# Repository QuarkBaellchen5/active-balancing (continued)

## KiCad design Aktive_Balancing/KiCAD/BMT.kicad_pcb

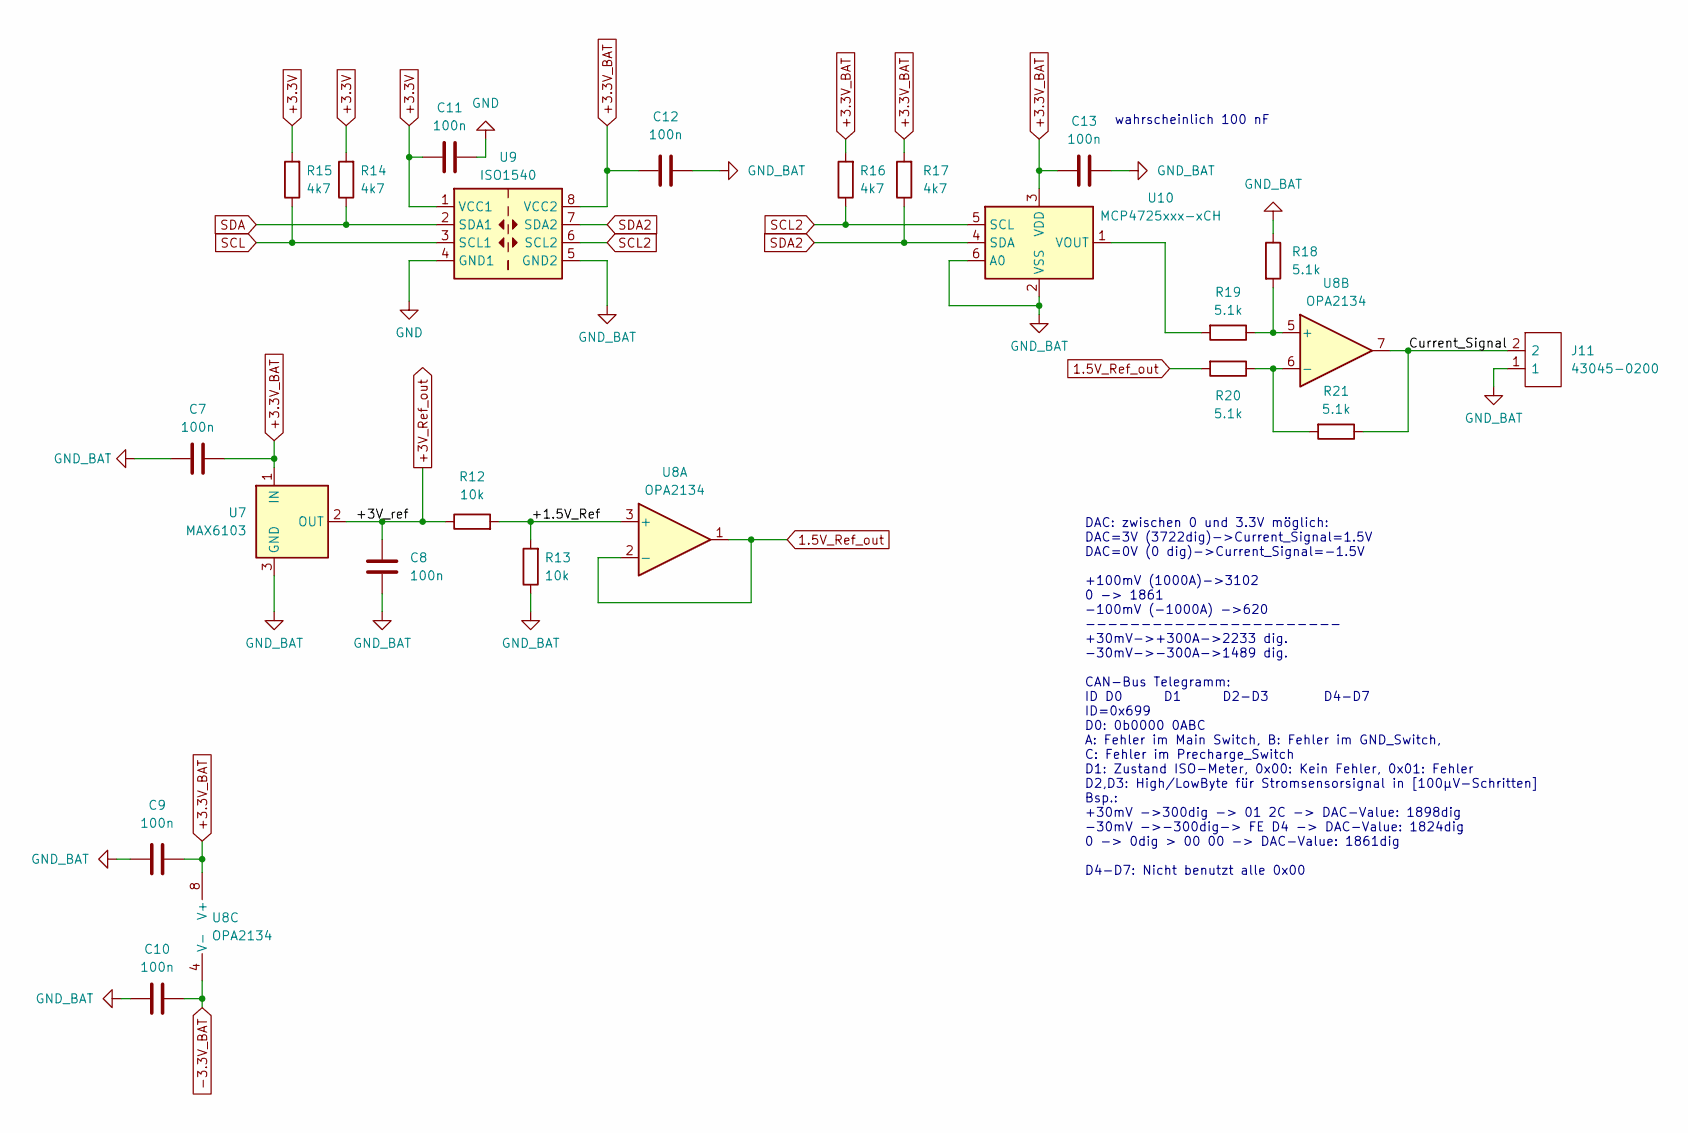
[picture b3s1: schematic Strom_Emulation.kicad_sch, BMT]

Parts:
C7, C8, C9, C10, C11, C12, C13: 100n; C_0603_1608Metric_Pad1.08x0.95mm_HandSolder
J11: 43045-0200; Manufacturer_Part_Number 43045-0200
R12, R13: 10k; R_0603_1608Metric
R14, R15, R16, R17: 4k7; R_0603_1608Metric
R18, R19, R20, R21: 5.1k; R_0603_1608Metric
U7: MAX6103; SOT-23
U8: OPA2134; SO-8_3.9x4.9mm_P1.27mm
U9: ISO1540; SOIC-8_3.9x4.9mm_P1.27mm; Mouser Part No 595-ISO1540DR
U10: MCP4725xxx-xCH; SOT-23-6; Mouser Part No 579-MCP4725A0TECH

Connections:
1.5V_Ref_out: R20.2, U8.1, U8.2 (-)
+3.3V: C11.1, R14.2, R15.2, U9.1 (VCC1); also elsewhere on the board
+3.3V_BAT: C7.2, C9.2, C12.1, C13.1, R16.2, R17.2, U7.1 (IN), U8.8 (V+), U9.8 (VCC2), U10.3 (VDD); also elsewhere on the board
+3V_Ref_out: C8.2, R12.1, U7.2 (OUT)
-3.3V_BAT: C10.2, U8.4 (V-); also elsewhere on the board
/Strom_Emulation/+1.5V_Ref: R12.2, R13.2, U8.3 (+)
/Strom_Emulation/Current_Signal: J11.2, R21.1, U8.7
GND: C11.2, U9.4 (GND1); also elsewhere on the board
GND_BAT: C7.1, C8.1, C9.1, C10.1, C12.2, C13.2, J11.1, R13.1, R18.1, U7.3 (GND), U9.5 (GND2), U10.2 (VSS), U10.6 (A0); also elsewhere on the board
unnamed: R18.2, R19.1, U8.5 (+)
unnamed: R20.1, R21.2, U8.6 (-)
unnamed: R19.2, U10.1 (VOUT)
SCL: R15.1, U9.3 (SCL1); also elsewhere on the board
SCL2: R16.1, U9.6 (SCL2), U10.5 (SCL)
SDA: R14.1, U9.2 (SDA1); also elsewhere on the board
SDA2: R17.1, U9.7 (SDA2), U10.4 (SDA)

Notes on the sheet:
wahrscheinlich 100 nF
DAC: zwischen 0 und 3.3V möglich: DAC=3V (3722dig)->Current_Signal=1.5V DAC=0V (0 dig)->Current_Signal=-1.5V +100mV (1000A)->3102 0 -> 1861 -100mV (-1000A) ->620 ----------------------- +30mV->+300A->2233 dig. -30mV->-300A->1489 dig. CAN-Bus Telegramm: ID D0 D1 D2-D3 D4-D7 ID=0x699 D0: 0b0000 0ABC 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

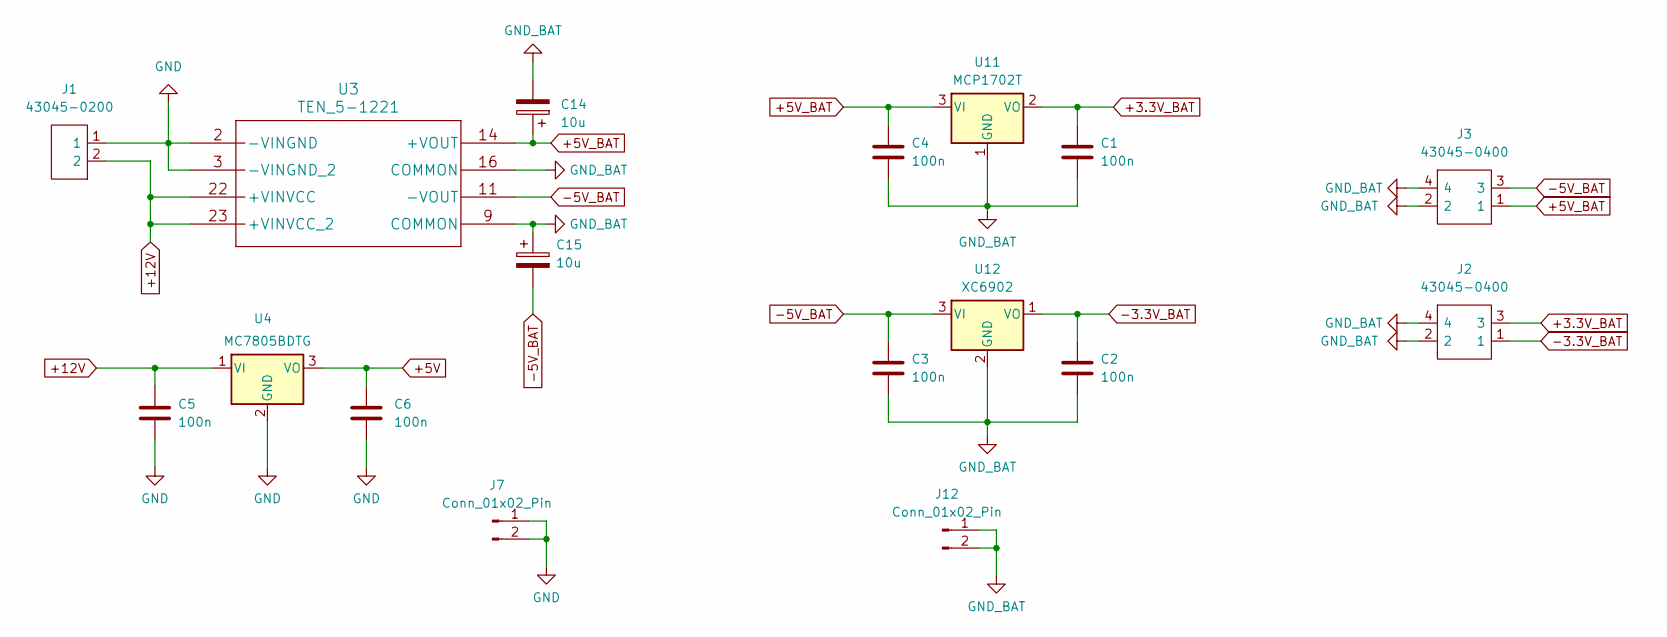
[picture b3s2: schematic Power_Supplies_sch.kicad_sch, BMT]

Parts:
C1, C2, C3, C4, C5, C6: 100n; C_0603_1608Metric_Pad1.08x0.95mm_HandSolder
C14, C15: 10u; CP_Elec_6.3x3.9
J1: 43045-0200; Manufacturer_Part_Number 43045-0200
J2, J3: 43045-0400; Manufacturer_Part_Number 43045-0400
J7, J12: Conn_01x02_Pin; PinHeader_1x02_P2.54mm_Vertical
U3: TEN_5-1221; TEN5_TRP
U4: MC7805BDTG; TO-252-3_TabPin4; Mouser Part No 863-MC7805CDTG
U11: MCP1702T; SOT-23; MANUFACTURER_PART_NUMBER MCP1702T-3302E/CB
U12: XC6902; SOT-23; MANUFACTURER_PART_NUMBER XC6902N331MR-G

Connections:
+3.3V_BAT: C1.1, J2.3, U11.2 (VO); also elsewhere on the board
+5V: C6.1, U4.3 (VO); also elsewhere on the board
+5V_BAT: C4.1, C14.1, J3.1, U3.14 (+VOUT), U11.3 (VI)
+12V: C5.1, J1.2, U3.22 (+VINVCC), U3.23 (+VINVCC_2), U4.1 (VI); also elsewhere on the board
-3.3V_BAT: C2.1, J2.1, U12.1 (VO); also elsewhere on the board
-5V_BAT: C3.1, C15.2, J3.3, U3.11 (-VOUT), U12.3 (VI)
GND: C5.2, C6.2, J1.1, J7.1, J7.2, U3.2 (-VINGND), U3.3 (-VINGND_2), U4.2 (GND); also elsewhere on the board
GND_BAT: C1.2, C2.2, C3.2, C4.2, C14.2, C15.1, J2.2, J2.4, J3.2, J3.4, J12.1, J12.2, U3.9 (COMMON), U3.16 (COMMON), U11.1 (GND), U12.2 (GND); also elsewhere on the board

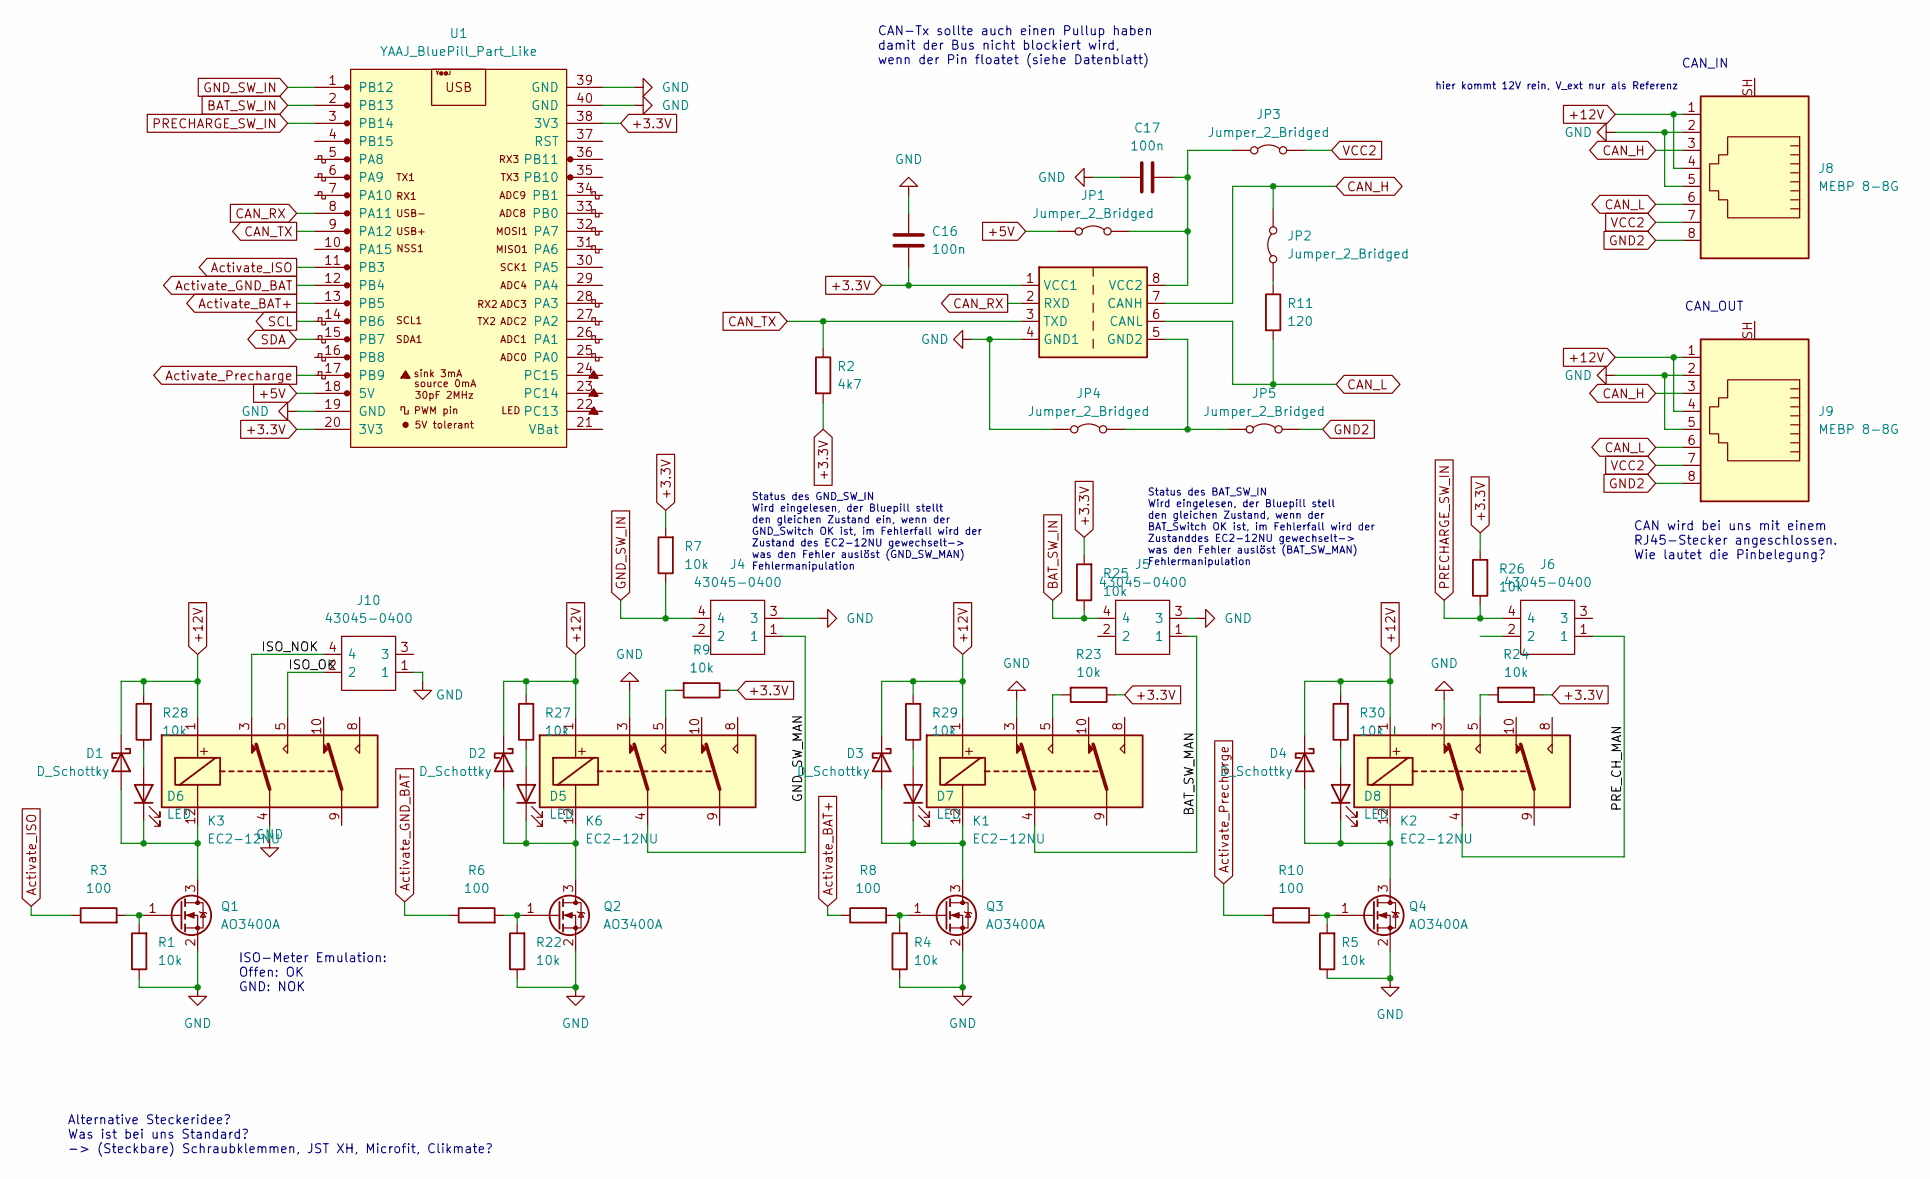
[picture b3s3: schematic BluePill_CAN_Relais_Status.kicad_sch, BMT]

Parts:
C16, C17: 100n; C_0603_1608Metric_Pad1.08x0.95mm_HandSolder
D1, D2, D3, D4: D_Schottky; D_SOD-323_HandSoldering; MANUFACTURER_PART_NUMBER 1N5819WS; LCSC Part Number C191023
D5, D6, D7, D8: LED; LED_0603_1608Metric_Pad1.05x0.95mm_HandSolder
J4, J5, J6, J10: 43045-0400; Manufacturer_Part_Number 43045-0400
J8, J9: MEBP 8-8G
JP1, JP2, JP3, JP4, JP5: Jumper_2_Bridged; PinHeader_1x02_P2.54mm_Vertical
K1, K2, K3, K6: EC2-12NU; Relay_DPDT_Kemet_EC2
Q1, Q2, Q3, Q4: AO3400A; SOT-23
R1, R4, R5, R7, R9, R22, R23, R24, R25, R26, R27, R28, R29, R30: 10k; R_0603_1608Metric
R2: 4k7; R_0603_1608Metric
R3, R6, R8, R10: 100; R_0603_1608Metric
R11: 120; R_0603_1608Metric
U1: YAAJ_BluePill_Part_Like; YAAJ_BluePill_1
U2: ISO1050DUB; SOP-8_6.62x9.15mm_P2.54mm

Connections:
+3.3V: C16.2, R2.2, R7.2, R9.1, R23.1, R24.1, R25.2, R26.2, U1.20 (3V3), U1.38 (3V3), U2.1 (VCC1); also elsewhere on the board
+5V: JP1.1 (A), U1.18 (5V); also elsewhere on the board
+12V: D1.1 (K), D2.1 (K), D3.1 (K), D4.1 (K), J8.1, J8.4, J9.1, J9.4, K1.1, K2.1, K3.1, K6.1, R27.2, R28.2, R29.2, R30.2; also elsewhere on the board
/BluePill_CAN_Relais_Status/BAT_SW_MAN: J5.1, K1.4
/BluePill_CAN_Relais_Status/GND_SW_MAN: J4.1, K6.4
/BluePill_CAN_Relais_Status/ISO_NOK: J10.4, K3.3
/BluePill_CAN_Relais_Status/ISO_OK: J10.2, K3.5
/BluePill_CAN_Relais_Status/PRE_CH_MAN: J6.1, K2.4
Activate_BAT+: R8.1, U1.13 (PB5)
Activate_GND_BAT: R6.1, U1.12 (PB4)
Activate_ISO: R3.1, U1.11 (PB3)
Activate_Precharge: R10.1, U1.17 (PB9)
BAT_SW_IN: J5.4, R25.1, U1.2 (PB13)
CAN_H: J8.3, J9.3, JP2.2 (B), U2.7 (CANH)
CAN_L: J8.6, J9.6, R11.2, U2.6 (CANL)
CAN_RX: U1.8 (PA11), U2.2 (RXD)
CAN_TX: R2.1, U1.9 (PA12), U2.3 (TXD)
GND: C16.1, C17.1, J4.3, J5.3, J8.2, J8.5, J9.2, J9.5, J10.1, JP4.1 (A), K1.3, K2.3, K3.4, K6.3, Q1.2 (S), Q2.2 (S), Q3.2 (S), Q4.2 (S), R1.1, R4.1, R5.1, R22.1, U1.19 (GND), U1.39 (GND), U1.40 (GND), U2.4 (GND1); also elsewhere on the board
GND2: J8.8, J9.8, JP5.2 (B)
GND_SW_IN: J4.4, R7.1, U1.1 (PB12)
unnamed: D1.2 (A), D6.1 (K), K3.12, Q1.3 (D)
unnamed: D2.2 (A), D5.1 (K), K6.12, Q2.3 (D)
unnamed: D3.2 (A), D7.1 (K), K1.12, Q3.3 (D)
unnamed: D4.2 (A), D8.1 (K), K2.12, Q4.3 (D)
unnamed: D5.2 (A), R27.1
unnamed: D6.2 (A), R28.1
unnamed: D7.2 (A), R29.1
unnamed: D8.2 (A), R30.1
unnamed: C17.2, JP1.2 (B), JP3.1 (A), U2.8 (VCC2)
unnamed: JP2.1 (A), R11.1
unnamed: JP4.2 (B), JP5.1 (A), U2.5 (GND2)
unnamed: K1.5, R23.2
unnamed: K2.5, R24.2
unnamed: K6.5, R9.2
unnamed: Q1.1 (G), R1.2, R3.2
unnamed: Q2.1 (G), R6.2, R22.2
unnamed: Q3.1 (G), R4.2, R8.2
unnamed: Q4.1 (G), R5.2, R10.2
PRECHARGE_SW_IN: J6.4, R26.1, U1.3 (PB14)
SCL: U1.14 (PB6); also elsewhere on the board
SDA: U1.15 (PB7); also elsewhere on the board
VCC2: J8.7, J9.7, JP3.2 (B)

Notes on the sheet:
Status des GND_SW_IN Wird eingelesen, der Bluepill stellt den gleichen Zustand ein, wenn der GND_Switch OK ist, im Fehlerfall wird der Zustand des EC2-12NU gewechselt-> was den Fehler auslöst (GND_SW_MAN) Fehlermanipulation
ISO-Meter Emulation: Offen: OK GND: NOK
CAN-Tx sollte auch einen Pullup haben damit der Bus nicht blockiert wird, wenn der Pin floatet (siehe Datenblatt)
Alternative Steckeridee? Was ist bei uns Standard? -> (Steckbare) Schraubklemmen, JST XH, Microfit, Clikmate?
CAN_OUT
CAN wird bei uns mit einem RJ45-Stecker angeschlossen. Wie lautet die Pinbelegung?
Status des BAT_SW_IN Wird eingelesen, der Bluepill stell den gleichen Zustand, wenn der BAT_Switch OK ist, im Fehlerfall wird der Zustanddes EC2-12NU gewechselt-> was den Fehler auslöst (BAT_SW_MAN) Fehlermanipulation
hier kommt 12V rein, V_ext nur als Referenz
CAN_IN

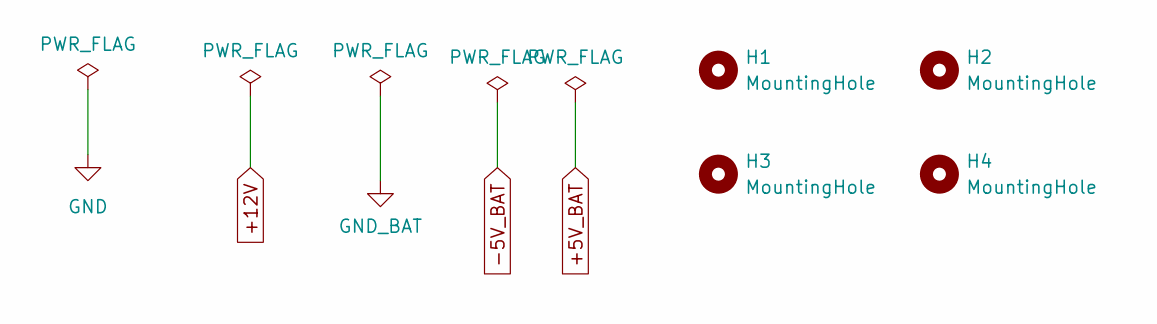
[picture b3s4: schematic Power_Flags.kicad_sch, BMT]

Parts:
H1, H2, H3, H4: MountingHole; MountingHole_3.2mm_M3_DIN965_Pad

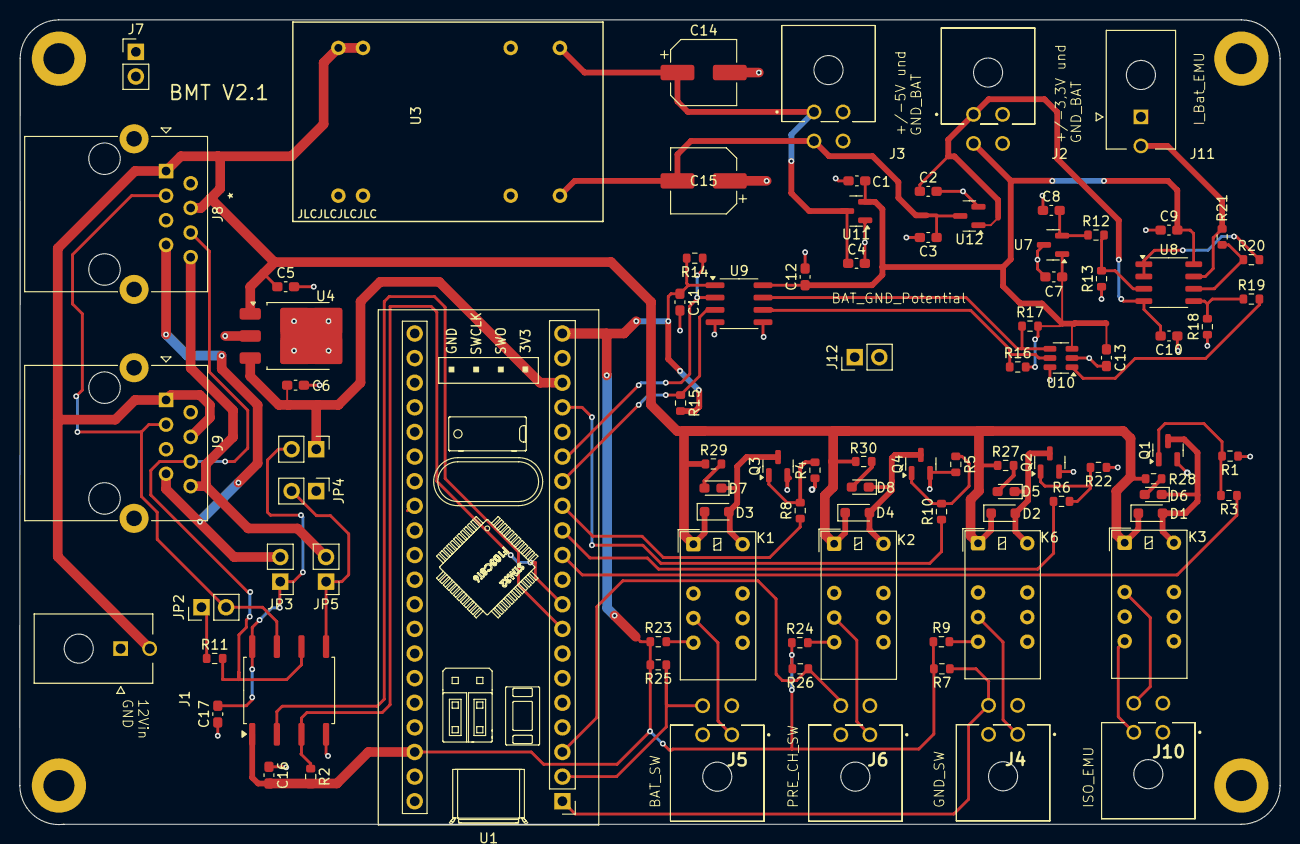
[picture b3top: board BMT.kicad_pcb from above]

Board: 2 copper layers, 130.0 x 83.0 mm, 94 parts (0 on the bottom side), 56 nets.

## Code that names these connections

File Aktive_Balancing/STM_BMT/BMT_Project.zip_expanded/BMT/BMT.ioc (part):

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Mcu.Name=STM32F103C(8-B)Tx
Mcu.Package=LQFP48
Mcu.UserName=STM32F103C8Tx
PA11.GPIOParameters=GPIO_PuPd
PA11.GPIO_PuPd=GPIO_PULLUP
PA11.Mode=CAN_Activate
PA11.Signal=CAN_RX
PA12.GPIOParameters=GPIO_Speed
PA12.GPIO_Speed=GPIO_SPEED_FREQ_HIGH
PA12.Mode=CAN_Activate
PA12.Signal=CAN_TX
PA13.Mode=Serial_Wire
PA13.Signal=SYS_JTMS-SWDIO
PA14.Mode=Serial_Wire
PA14.Signal=SYS_JTCK-SWCLK
PB12.GPIOParameters=GPIO_Label
PB12.GPIO_Label=GND_SW_IN
PB12.Signal=GPIO_Input
PB13.GPIOParameters=GPIO_Label
PB13.GPIO_Label=BAT_SW_in
PB13.Signal=GPIO_Input
PB14.GPIOParameters=GPIO_Label
PB14.GPIO_Label=PreCh_SW_in
PB14.Signal=GPIO_Input
PB3.GPIOParameters=GPIO_Label
PB3.GPIO_Label=Activate_ISO
PB3.Signal=GPIO_Output
PB4.GPIOParameters=GPIO_Label
PB4.GPIO_Label=Activate_GND_BAT
PB4.Signal=GPIO_Output
PB5.GPIOParameters=GPIO_Label
PB5.GPIO_Label=Avtivate_Bat_Plus
PB5.Signal=GPIO_Output
PB6.GPIOParameters=GPIO_Speed
PB6.GPIO_Speed=GPIO_SPEED_FREQ_HIGH
PB6.Mode=I2C
PB6.Signal=I2C1_SCL
PB7.GPIOParameters=GPIO_Speed
PB7.GPIO_Speed=GPIO_SPEED_FREQ_HIGH
PB7.Mode=I2C
PB7.Signal=I2C1_SDA
PB9.GPIOParameters=GPIO_Label
PB9.GPIO_Label=Acivate_Precharche
PB9.Signal=GPIO_Output
PD0-OSC_IN.Mode=HSE-External-Oscillator
PD0-OSC_IN.Signal=RCC_OSC_IN
PD1-OSC_OUT.Mode=HSE-External-Oscillator
PD1-OSC_OUT.Signal=RCC_OSC_OUT
RCC.SYSCLKFreq_VALUE=72000000
RCC.SYSCLKSource=RCC_SYSCLKSOURCE_PLLCLK
board=custom

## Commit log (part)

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2026-04-02 add gittignore for LTSpice
2026-04-06 Eingerichtet
2026-04-06 temp save
2026-04-06 OPamp ersetzt durch realen OP
    Der Opamp2 hab ich jetzt ersetzt gegen einen realen OP den LT1007
2026-04-06 Schalter gegen Mosfet
    versucht den schalter zu tauschen aber der strom wird dann nicht mehr geregelt
2026-04-06 schalter getauscht
2026-04-07 added models for LT
    Dateien hinzugefügt
    für Infineon Fets
2026-04-07 krams weg
2026-04-08 Si7336ADP
2026-04-08 Janne Highside Test hinzu
2026-04-08 Modell für Baustein VOM1271
2026-04-10 mosfet action
2026-04-10 KiCad Directory hinzugefügt
2026-04-10 optokoppler probiert
2026-04-19 Bauteilliste und erste Datasheets
2026-04-20 Aufgabenbeschreibung
2026-04-20 Simulation pptimiert
    Highside Lowside Mosfet
    rückkopplugn über OP
2026-04-20 kicad angefangen
2026-04-21 Erste Schalplan Skizze mit Fragen an Weber
2026-04-21 Mit I2C Koppler neu
2026-04-21 kicad änderungen
2026-04-21 kicad weiter
2026-04-22 kicad
2026-04-23 STM PRojekt
2026-04-24 Neue Datasheets
2026-04-24 Neue Bestelliste
2026-04-25 Kicad klopf klopf klopf
2026-04-30 kicad widerstand
2026-04-30 kicad gewurstel
2026-04-30 qwertzuiop
2026-04-30 Projektmanagement
2026-05-04 kicad klopf klopf
2026-05-04 kicad weiter weiter
2026-05-05 aktualisierte sachen
2026-05-07 fehler im Kicad
2026-05-12 kicad bla bla
2026-05-13 neuneuneu
2026-05-13 Neue Bestellliste
2026-05-13 kicad export
2026-05-13 excel datei krams
2026-05-16 Footprintts
2026-05-16 footprints
2026-05-17 Kicad Footprints
2026-05-17 footprints zuggewiesen
2026-05-19 Neue Datasheets und Leistungsberechnung
2026-05-19 hochlaaaden
2026-05-19 layout
2026-05-20 Bestellliste_V5
2026-05-21 mosfet symbol
2026-05-21 Optokram und Widerstände
2026-05-21 kicad sub strukturen
    Den schaltplan in kleinere aufgeteilt
2026-05-29 kicad bom
2026-05-31 egal
2026-05-31 Bestelliste V6
2026-06-01 kondensator an den 3.3V µc
    den kondensator an der Stiftleiste vom mikrokontroller geändert zu einem Bulk kondensator
2026-06-03 neu datasheet
2026-06-03 Neue Liste
2026-06-07 layour
2026-06-07 layout
    Komponenten geordnet
2026-06-11 BM107 V6 Dateien
    Geht Gideon garnichts an!!!
2026-06-11 Schaltung Review + Layout
    Schaltung Review + Layout
2026-06-11 wertz
    wert
2026-06-11 geht gideon immer noch nichts an
2026-06-12 neuer stand
2026-06-12 Bisschen sortiert und so
2026-06-15 shunt update
2026-06-15 qwertzui
    qwertzu
2026-06-15 shunt datasheet
2026-06-15 neuneuenu
2026-06-15 Regelkreis sortiert
2026-06-16 test
    test
2026-06-16 mein stand gestern abend
2026-06-16 Layout kompakter gemacht
    Ich habe die Sektion mit dem Mosfets gemacht. Weber hat es nicht anders gewollt...
2026-06-17 hassplatine
2026-06-17 Microcontroller geroutet
2026-06-18 NEuneuenuenbeuebu
2026-06-22 beschriftung der pins
2026-06-22 alles neu
2026-06-22 opto verschobnen und krams
2026-06-23 bm107 neu
2026-06-23 qwert
    qer
2026-06-23 Layout fürs erste fertig gemacht
    Erste vollständig geroutete Version; Silkscreens sind auch halbwegs gut
2026-06-23 quetschen
    brücken getauscht
2026-06-23 ASDF
    ASDF
2026-06-24 bisschen abstände und so
2026-06-24 bm107 abgabe
2026-06-24 Kleine Änderung canbus
2026-06-24 Kleine Änderung an BM107 V6 BOM
    Einzelpreis
2026-06-24 qwer
    we
2026-06-25 review
2026-06-25 Differenzverstärker
    Auslegung eines Differenzverstärkers
2026-06-26 Vorläufige finale Version
    Diese Version soll in die Fertigung gehen.
